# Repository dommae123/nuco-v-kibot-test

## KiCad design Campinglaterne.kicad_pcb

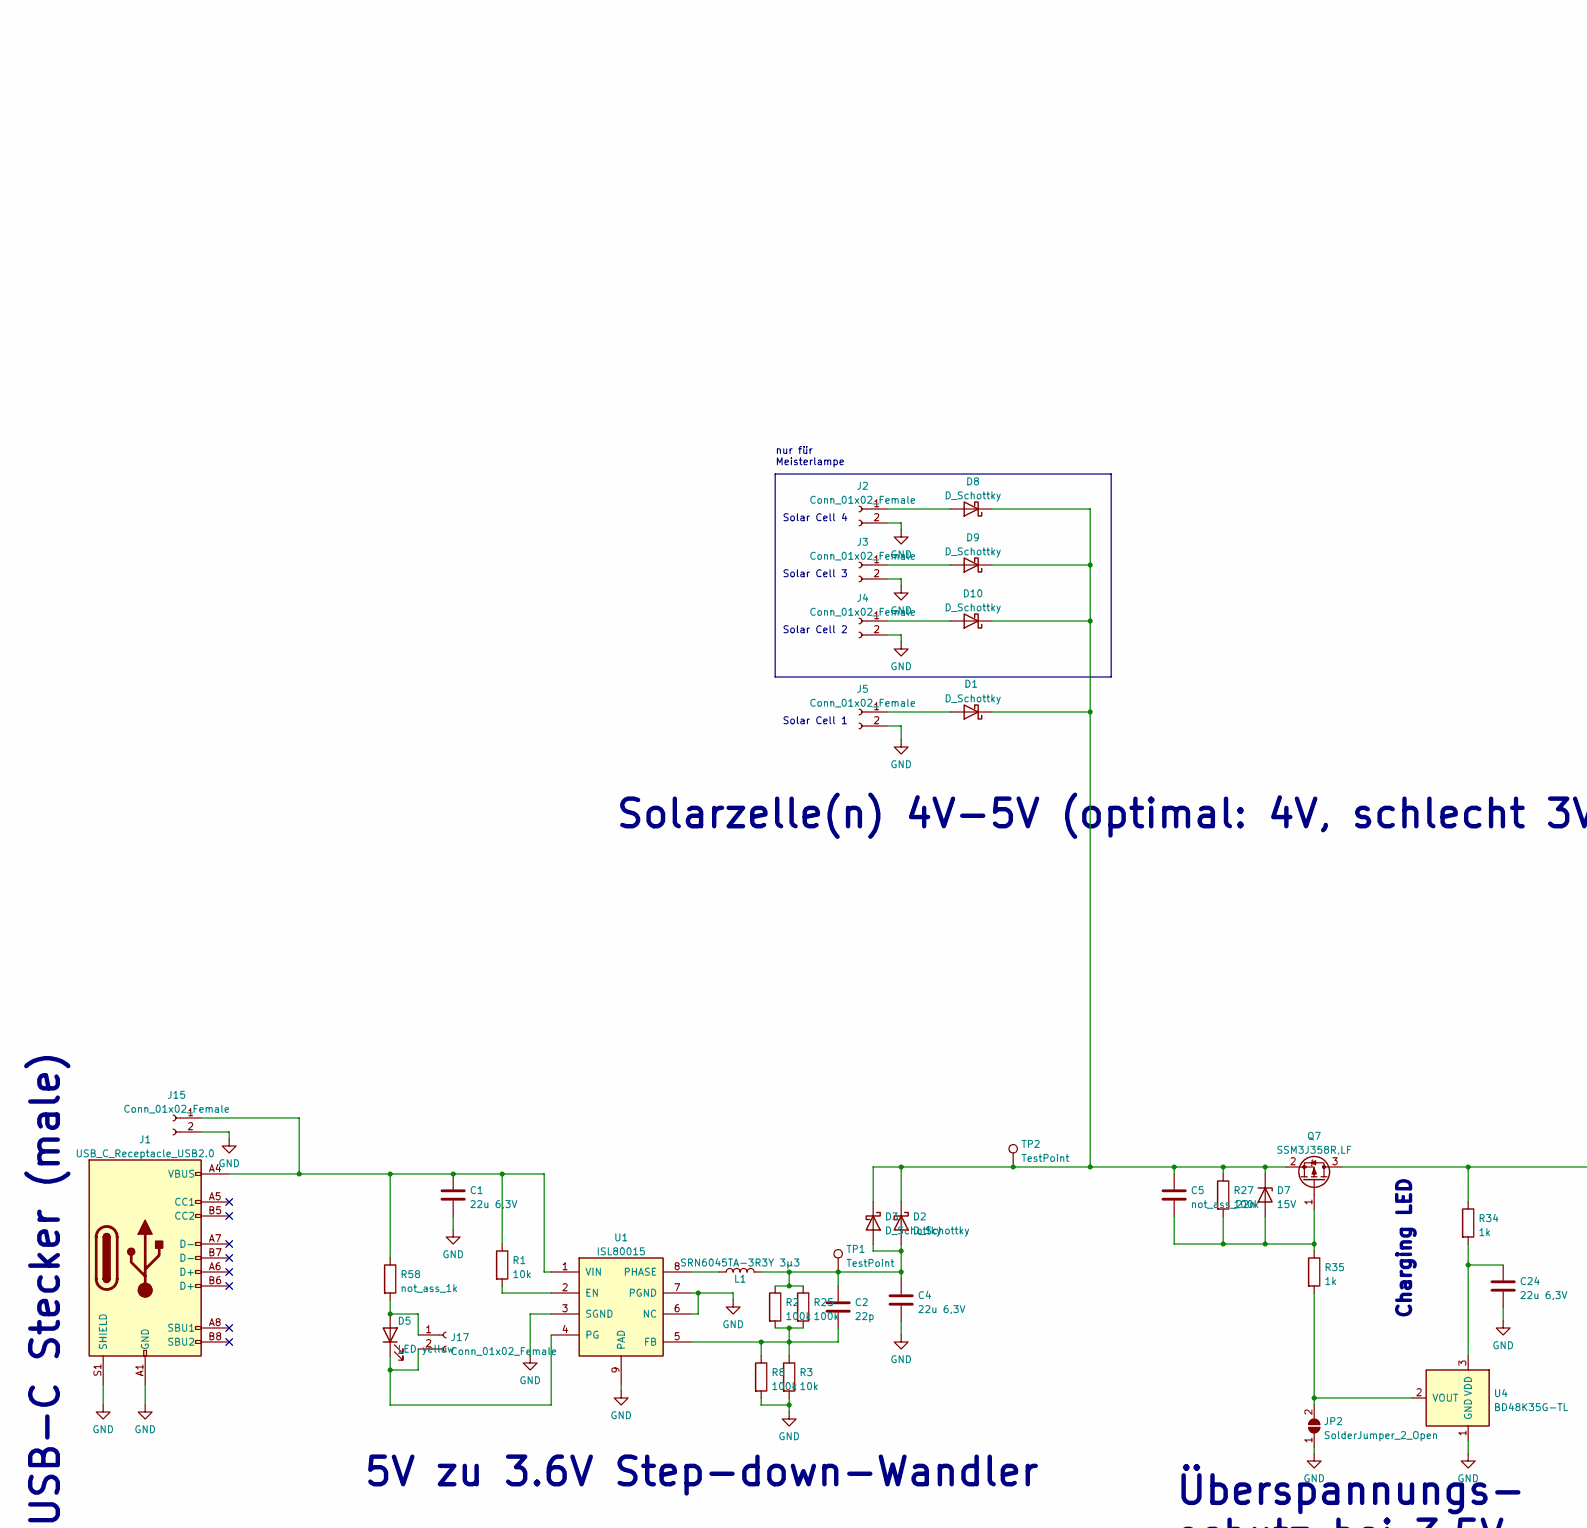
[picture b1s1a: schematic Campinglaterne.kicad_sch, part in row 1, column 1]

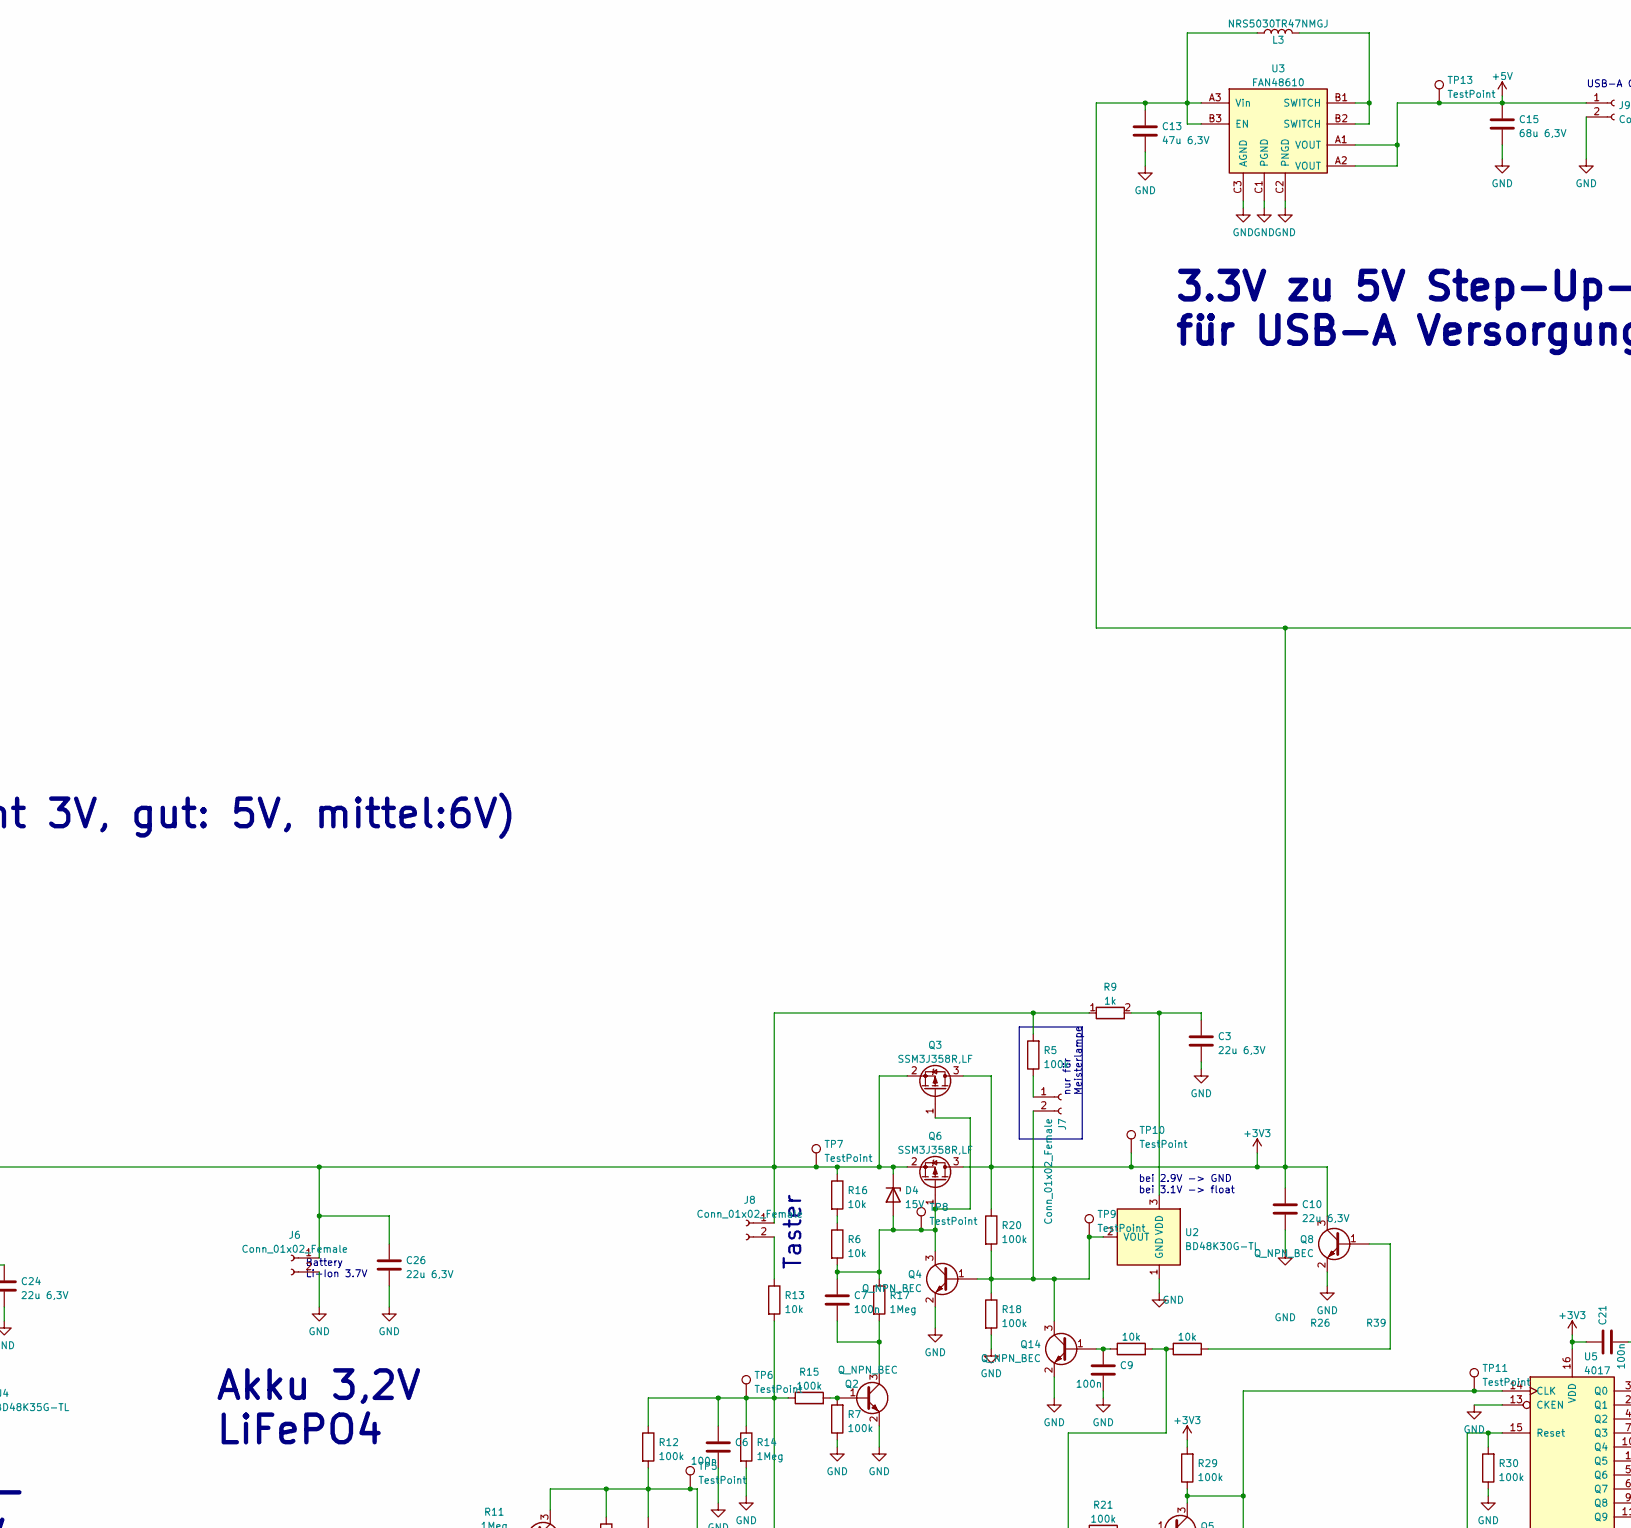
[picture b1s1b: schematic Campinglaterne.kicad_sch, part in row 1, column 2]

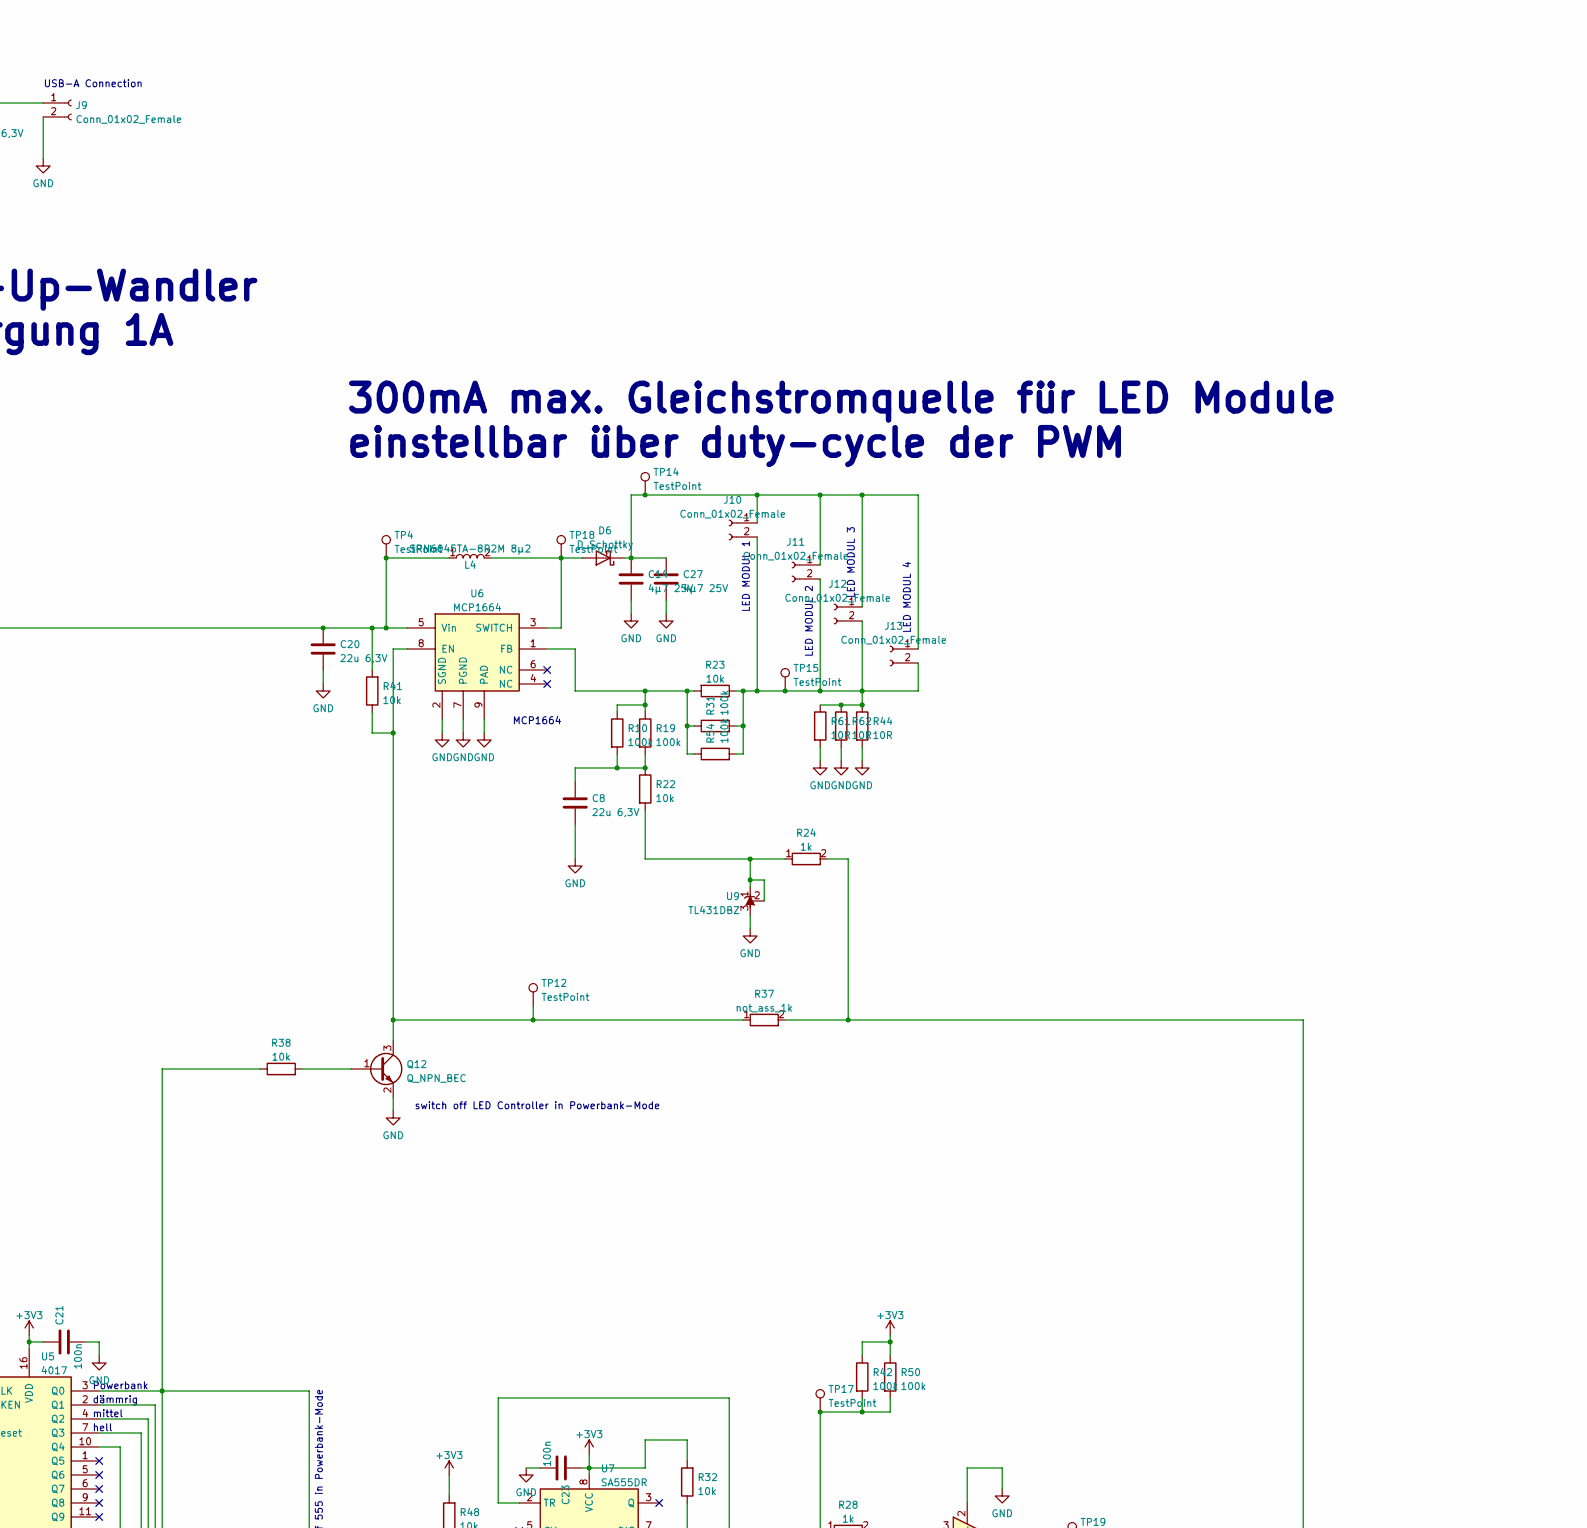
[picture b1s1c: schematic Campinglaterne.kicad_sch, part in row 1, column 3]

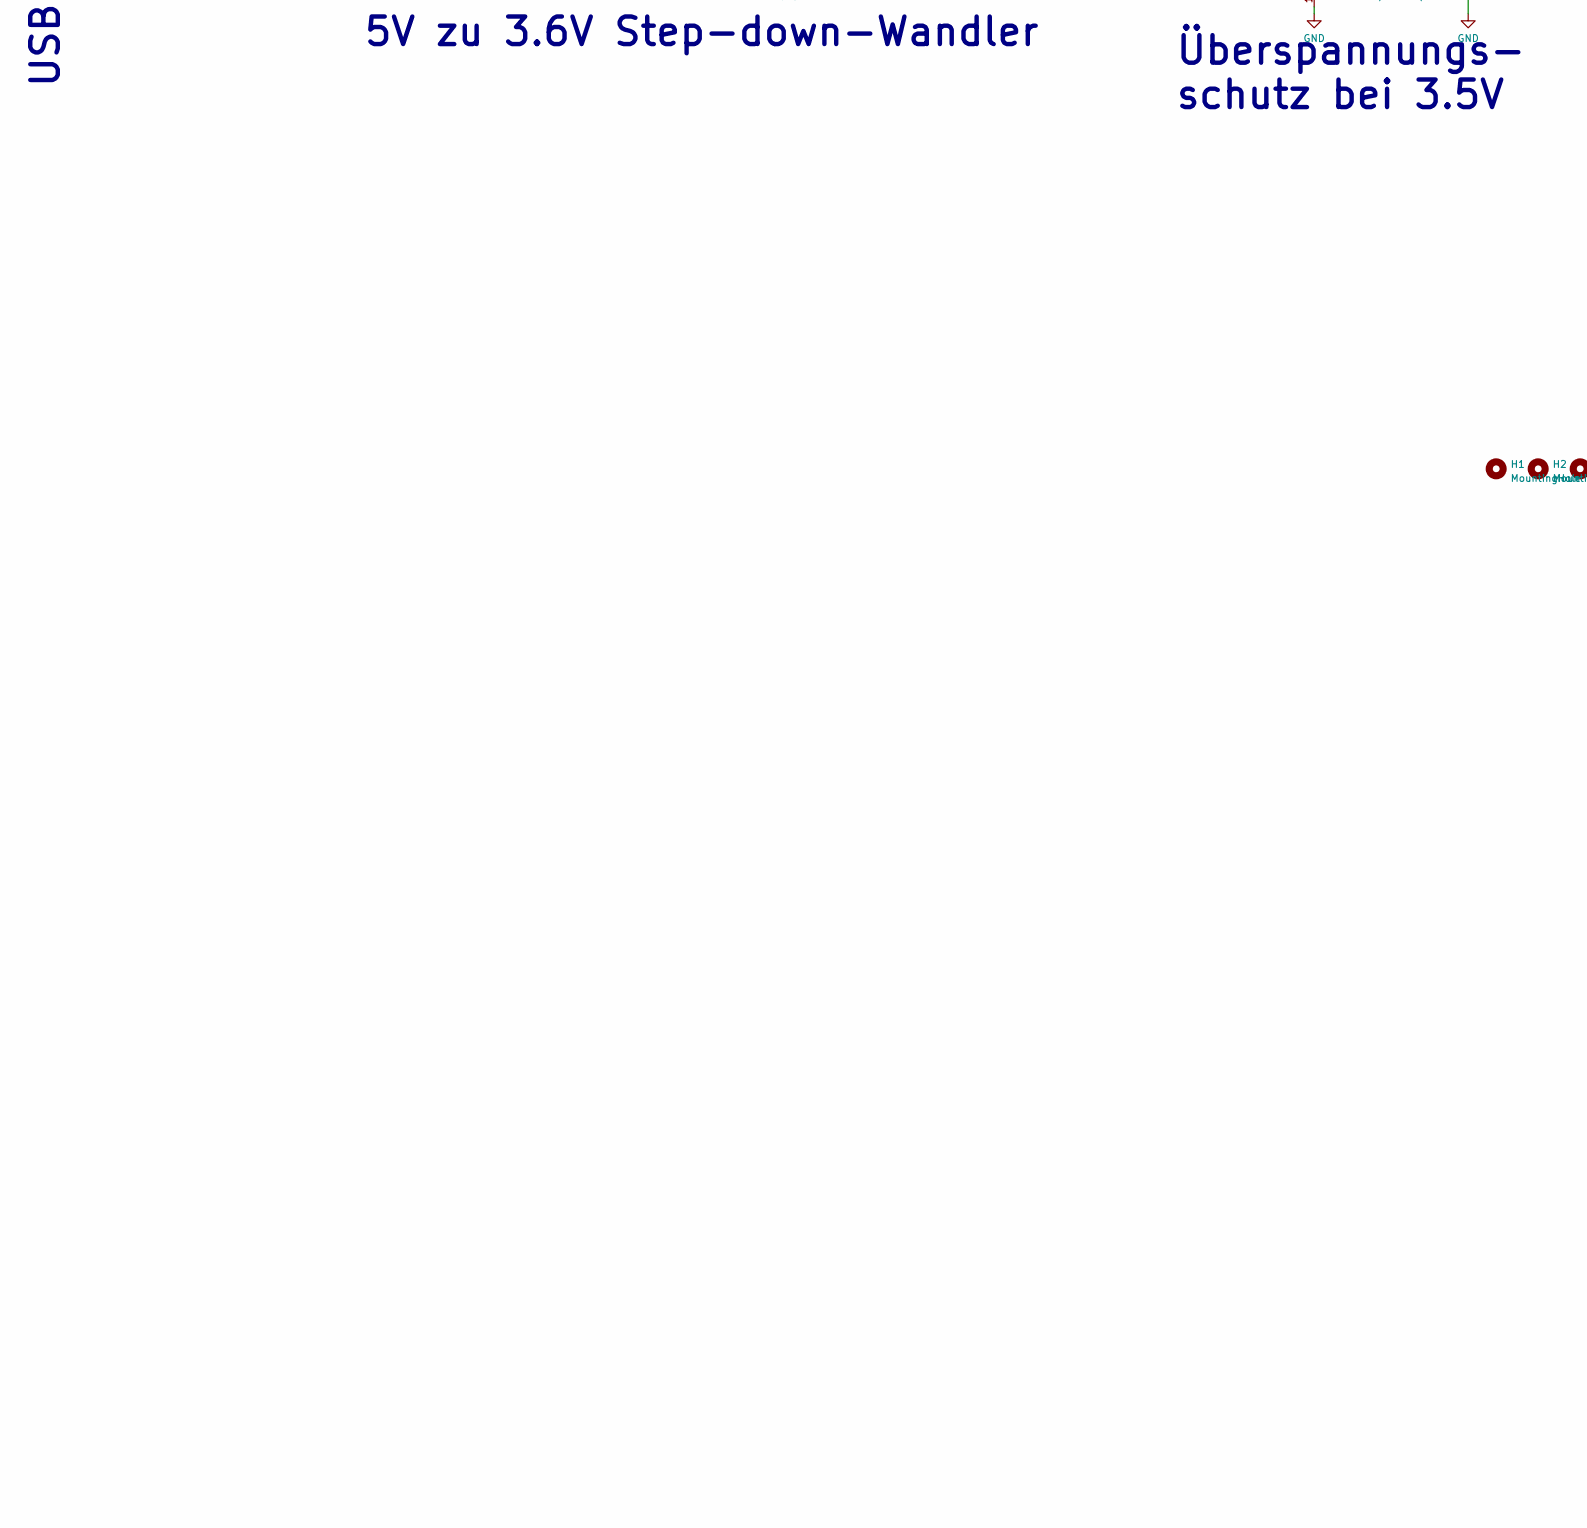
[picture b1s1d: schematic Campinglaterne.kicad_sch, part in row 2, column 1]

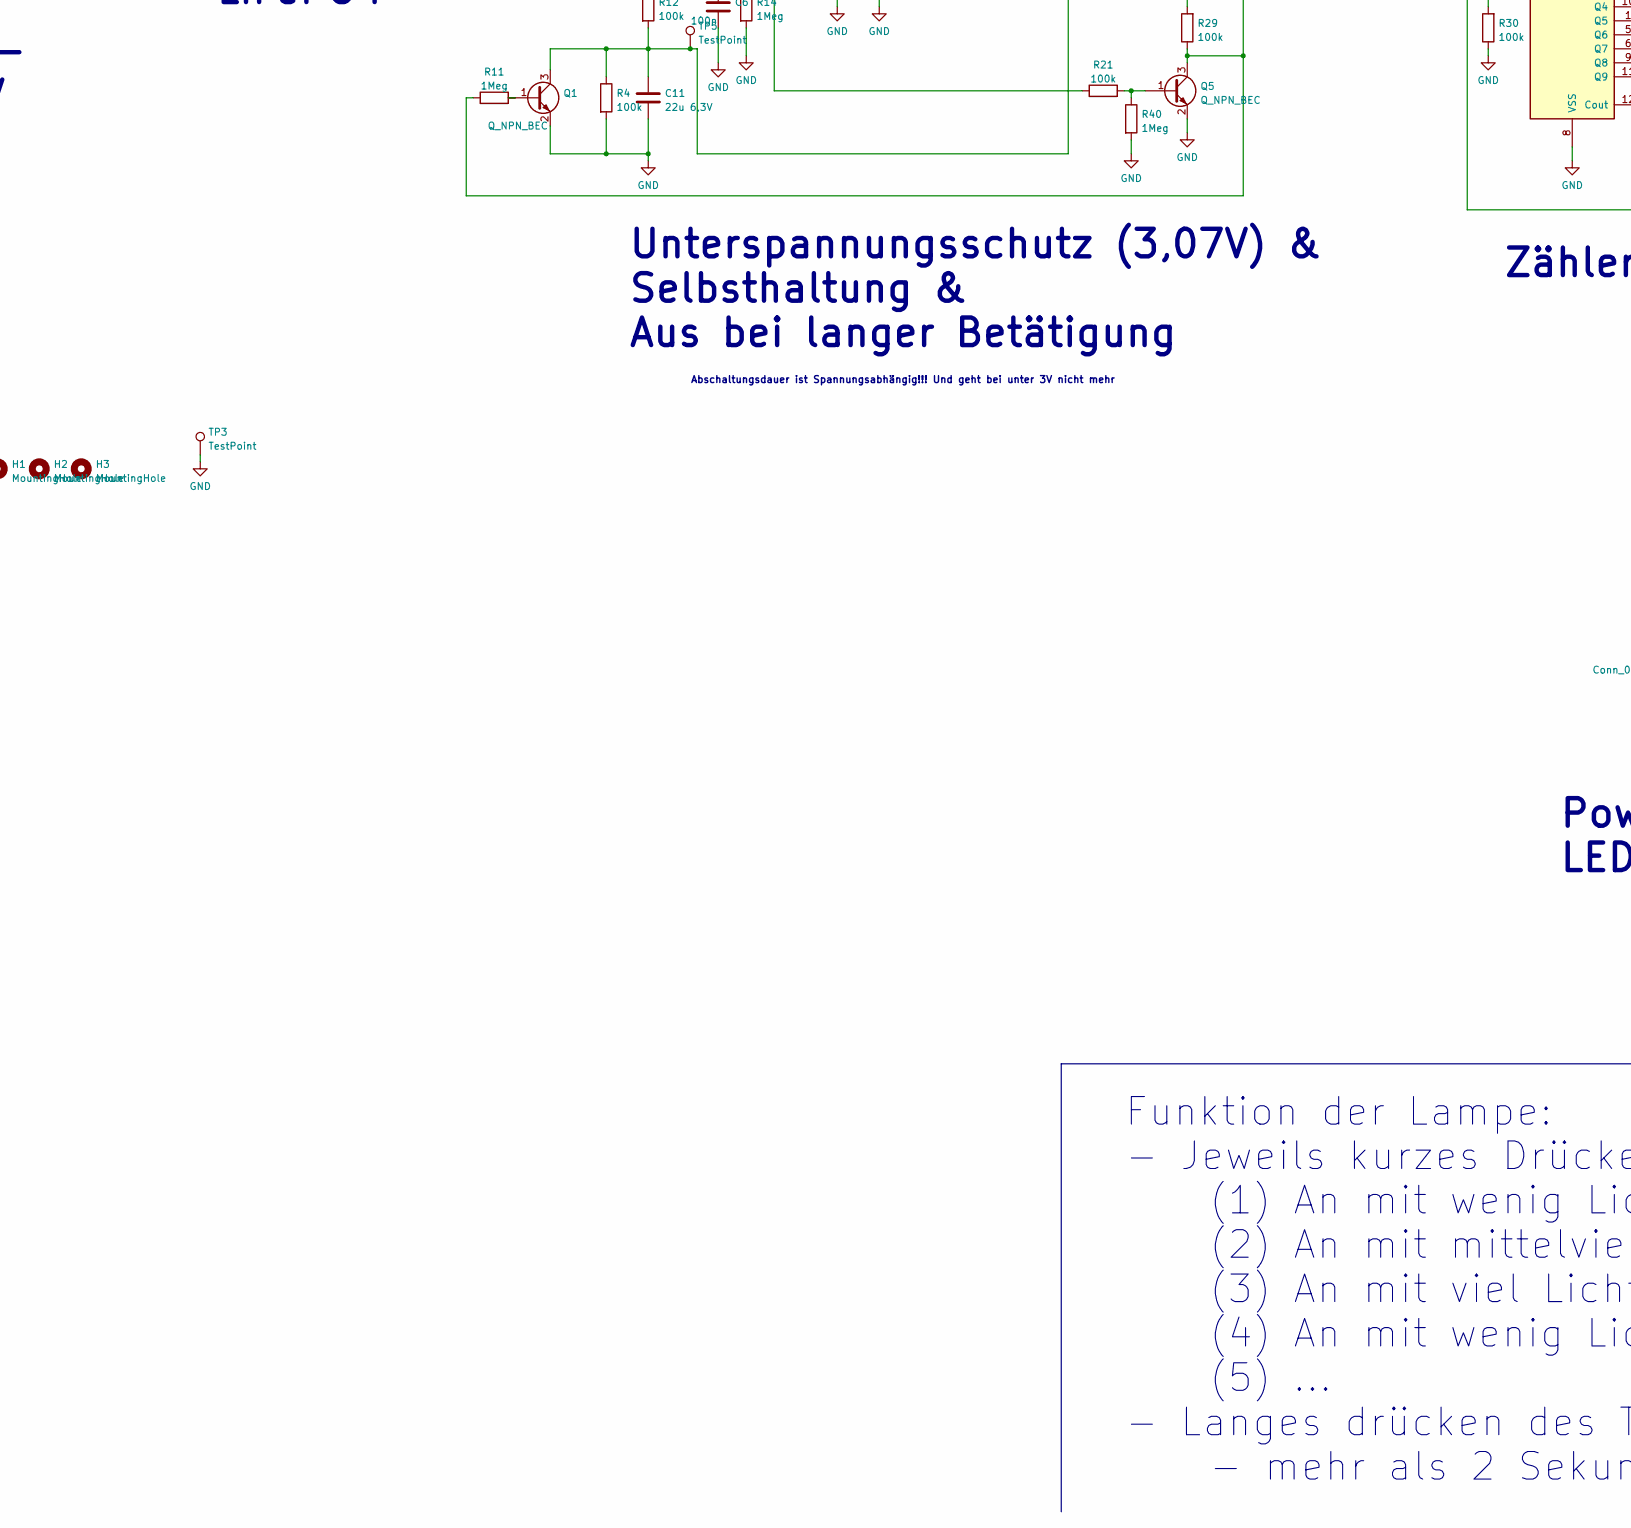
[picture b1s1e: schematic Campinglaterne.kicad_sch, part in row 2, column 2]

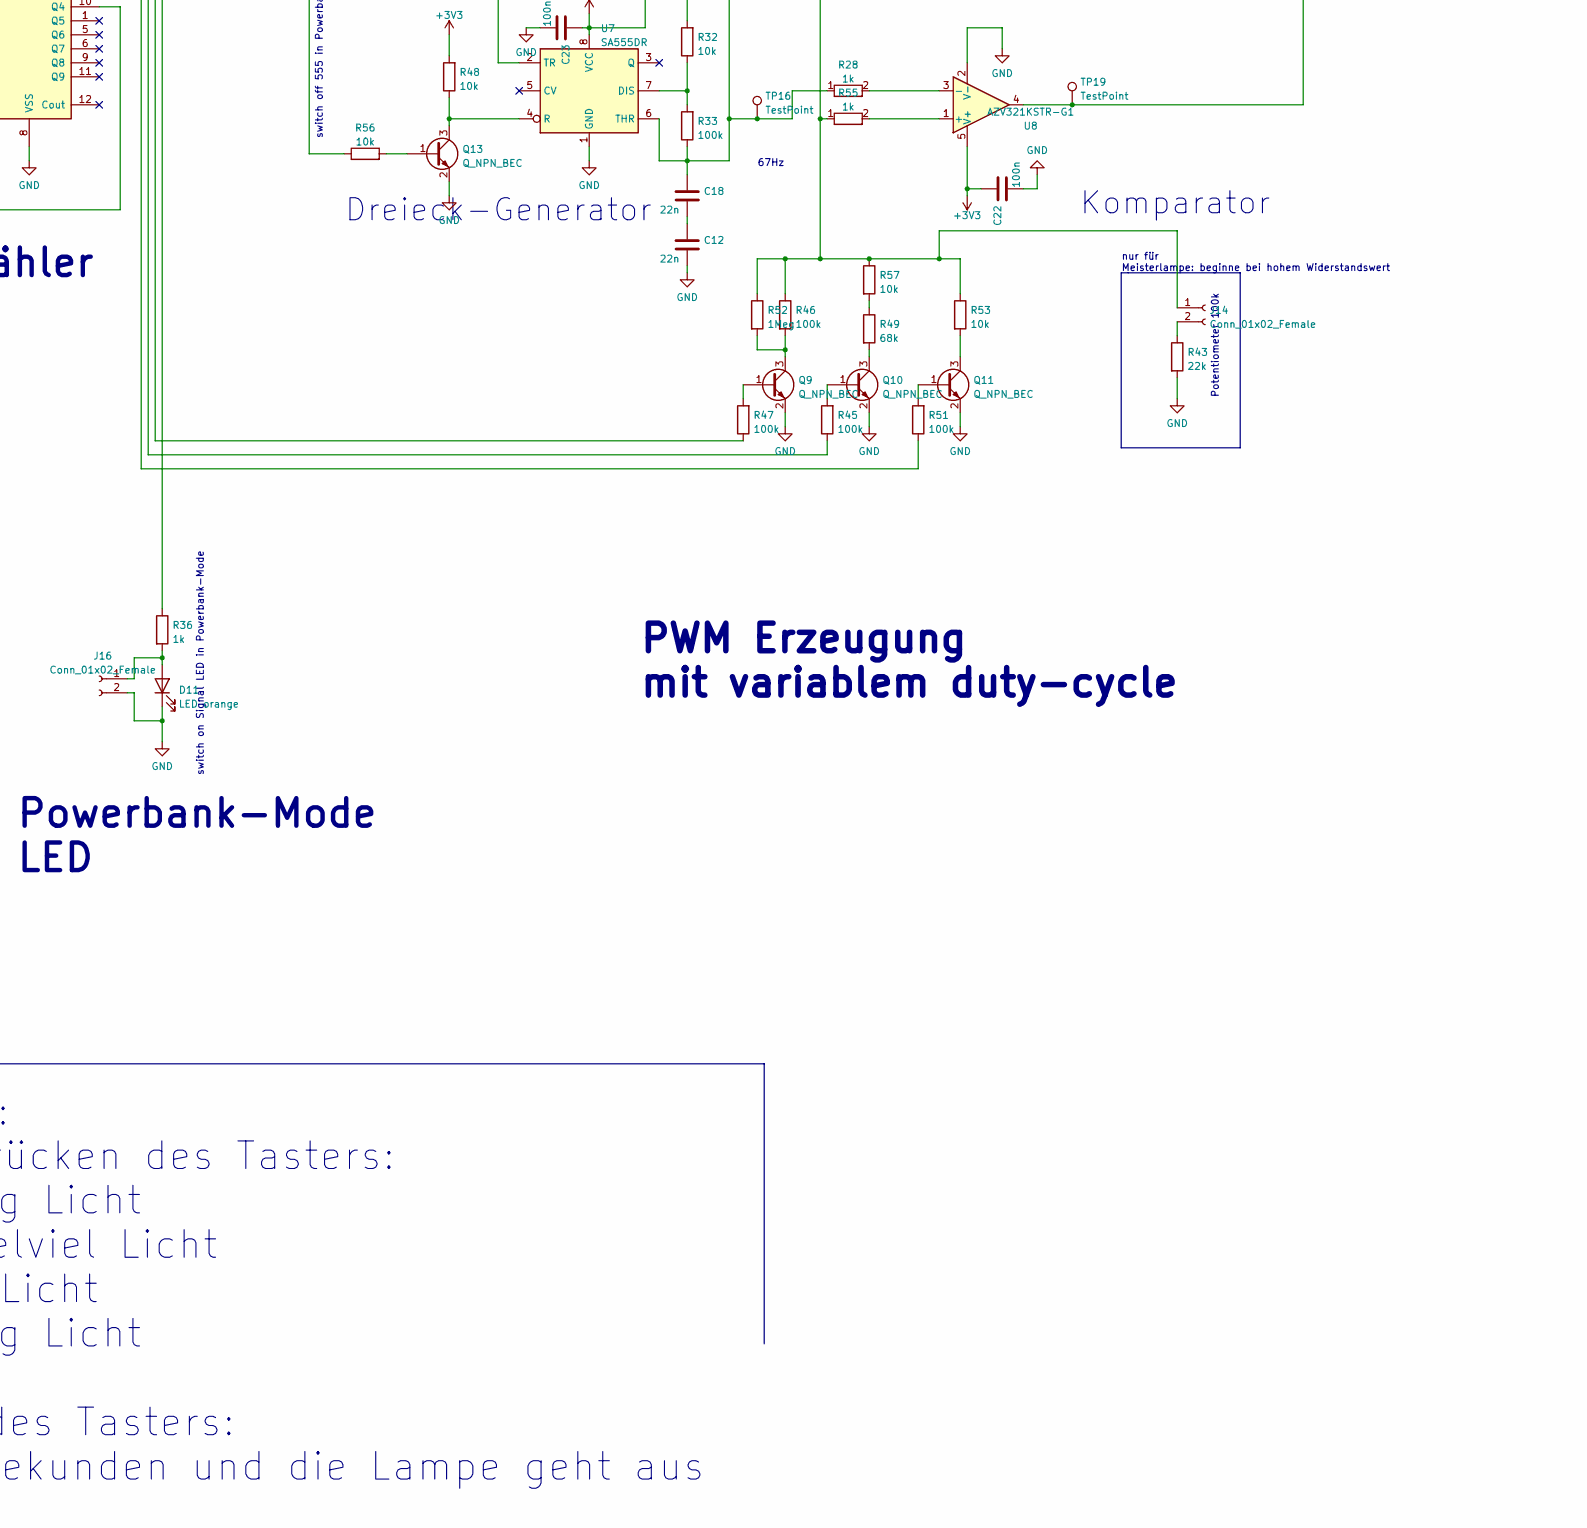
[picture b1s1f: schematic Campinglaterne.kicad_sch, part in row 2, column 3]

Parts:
C1, C3, C4, C8, C10, C11, C20, C24, C26: 22u 6,3V; C_0603_1608Metric
C2: 22p; C_0603_1608Metric
C5: not_ass_22n; C_0603_1608Metric
C6, C7, C9, C21, C22, C23: 100n; C_0603_1608Metric
C12, C18: 22n; C_0603_1608Metric
C13: 47u 6,3V; C_0603_1608Metric
C14, C27: 4µ7 25V; C_0805_2012Metric
C15: 68u 6,3V; C_0603_1608Metric
D1, D8, D9, D10: D_Schottky; D_0805_2012Metric
D2, D3, D6: D_Schottky; D_SMB
D4, D7: 15V; D_SOT-23_ANK
D5: LED yellow; LED_0603_1608Metric
D11: LED orange; LED_0603_1608Metric
H1, H2, H3: MountingHole; MountingHole_3.2mm_M3_ISO14580
J1: USB_C_Receptacle_USB2.0; USB_C_Receptacle_GCT_USB4085
J2, J3, J4, J5, J6, J7, J8, J9, J10, J11, J12, J13, J14, J15, J16, J17: Conn_01x02_Female; PinSocket_1x02_P2.54mm_Vertical
JP2: SolderJumper_2_Open; SolderJumper-2_P1.3mm_Open_RoundedPad1.0x1.5mm
L1: SRN6045TA-3R3Y 3µ3; L_Bourns_SRN6045TA
L3: NRS5030TR47NMGJ; L_Taiyo-Yuden_NR-50xx
L4: SRN6045TA-8R2M 8µ2; L_Bourns_SRN6045TA
Q1, Q2, Q4, Q5, Q8, Q9, Q10, Q11, Q12, Q13, Q14: Q_NPN_BEC; SOT-23
Q3, Q6, Q7: SSM3J358R,LF; SOT-23
R1, R3, R6, R13, R16, R22, R23, R26, R32, R38, R39, R41, R48, R53, R56, R57: 10k; R_0603_1608Metric
R2, R4, R5, R7, R8, R10, R12, R15, R18, R19, R20, R21, R25, R27, R29, R30, R31, R33, R42, R45, R46, R47, R50, R51, R54: 100k; R_0603_1608Metric
R9, R24, R28, R34, R35, R36, R55: 1k; R_0603_1608Metric
R11, R14, R17, R40, R52: 1Meg; R_0603_1608Metric
R37, R58: not_ass_1k; R_0603_1608Metric
R43: 22k; R_0603_1608Metric
R44, R61, R62: 10R; R_0603_1608Metric
R49: 68k; R_0603_1608Metric
TP1, TP2, TP3, TP4, TP5, TP6, TP7, TP8, TP9, TP10, TP11, TP12, TP13, TP14, TP15, TP16, TP17, TP18, TP19: TestPoint; TestPoint_THTPad_2.0x2.0mm_Drill1.0mm
U1: ISL80015; DFN-8-1EP_2x2mm_P0.5mm_EP0.8x1.6mm
U2: BD48K30G-TL; SOT-23
U3: FAN48610; Maxim_WLP-9_1.595x1.415_Layout3x3_P0.4mm_Ball0.27mm_Pad0.25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
U4: BD48K35G-TL; SOT-23
U5: 4017; SOIC-16_4.55x10.3mm_P1.27mm
U6: MCP1664; DFN-8-1EP_3x2mm_P0.5mm_EP1.3x1.5mm
U7: SA555DR; SOIC-8_3.9x4.9mm_P1.27mm
U8: AZV321KSTR-G1; SOT-23-5
U9: TL431DBZ; SOT-23

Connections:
+3V3: C10.1, C13.1, C20.1, C21.1, C22.1, C23.1, L3.1, L4.1, Q3.3 (D), Q6.3 (D), Q8.3 (C), R20.1, R29.2, R32.2, R41.2, R42.1, R48.2, R50.1, TP4.1, TP10.1, U3.A3 (Vin), U3.B3 (EN), U5.16 (VDD), U6.5 (Vin), U7.8 (VCC), U8.5 (V+)
+5V: C15.1, J9.1, TP13.1, U3.A1 (VOUT), U3.A2 (VOUT)
GND: C1.2, C3.2, C4.2, C6.2, C8.2, C9.2, C10.2, C11.2, C12.2, C13.2, C14.2, C15.2, C20.2, C21.2, C22.2, C23.2, C24.2, C26.2, C27.2, D11.1 (K), J1.A1 (GND), J1.A12 (GND), J1.B1 (GND), J1.B12 (GND), J1.S1 (SHIELD), J2.2, J3.2, J4.2, J5.2, J6.2, J9.2, J15.2, J16.2, JP2.1 (A), Q1.2 (E), Q2.2 (E), Q4.2 (E), Q5.2 (E), Q8.2 (E), Q9.2 (E), Q10.2 (E), Q11.2 (E), Q12.2 (E), Q13.2 (E), Q14.2 (E), R3.2, R4.2, R7.1, R8.2, R14.2, R18.2, R30.1, R40.2, R43.2, R44.2, R61.2, R62.2, TP3.1, U1.3 (SGND), U1.6 (NC), U1.7 (PGND), U1.9 (PAD), U2.1 (GND), U3.C1 (PGND), U3.C2 (PNGD), U3.C3 (AGND), U4.1 (GND), U5.8 (VSS), U5.13 (CKEN), U6.2 (SGND), U6.7 (PGND), U6.9 (PAD), U7.1 (GND), U8.2 (V-), U9.3 (A)
unnamed: C1.1, J1.A4 (VBUS), J1.A9 (VBUS), J1.B4 (VBUS), J1.B9 (VBUS), J15.1, R1.1, R58.1, U1.1 (VIN)
unnamed: C2.1, C4.1, D2.2 (A), D3.2 (A), L1.2, R2.1, R25.1, TP1.1
unnamed: C2.2, R2.2, R3.1, R8.1, R25.2, U1.5 (FB)
unnamed: C3.1, R9.2, U2.3 (VDD)
unnamed: C5.1, D1.1 (K), D2.1 (K), D3.1 (K), D7.1 (K), D8.1 (K), D9.1 (K), D10.1 (K), Q7.2 (S), R27.1, TP2.1
unnamed: C5.2, D7.2 (A), Q7.1 (G), R27.2, R35.1
unnamed: C6.1, R12.1, R13.2, R14.1, R15.1, R21.1, TP6.1
unnamed: C7.1, D4.2 (A), Q3.1 (G), Q4.3 (C), Q6.1 (G), R6.2, R17.1, TP8.1
unnamed: C7.2, Q2.3 (C), R17.2
unnamed: C8.1, R10.2, R19.2, R22.1
unnamed: C9.1, Q14.1 (B), R26.1
unnamed: C11.1, Q1.3 (C), R4.1, R12.2, R26.2, R39.1, TP5.1
unnamed: C12.1, C18.2
unnamed: C14.1, C27.1, D6.1 (K), J10.1, J11.1, J12.1, J13.1, TP14.1
unnamed: C18.1, R28.1, R33.1, TP16.1, U7.2 (TR), U7.6 (THR)
unnamed: C24.1, R34.2, U4.3 (VDD)
unnamed 19: C26.1, D4.1 (K), J6.1, J8.1, Q3.2 (S), Q6.2 (S), Q7.3 (D), R5.2, R9.1, R16.1, R34.1, TP7.1; also elsewhere on the board
unnamed: D1.2 (A), J5.1
unnamed: D6.2 (A), L4.2, TP18.1, U6.3 (SWITCH)
unnamed: D8.2 (A), J2.1
unnamed: D9.2 (A), J3.1
unnamed: D10.2 (A), J4.1
unnamed: D11.2 (A), J16.1, R36.2
unnamed 26: D5.2 (A), J17.1, R58.2; also elsewhere on the board
unnamed: J7.1, R5.1
unnamed: J7.2, Q4.1 (B), Q14.3 (C), R18.1, R20.2, TP9.1, U2.2 (VOUT)
unnamed: J8.2, R13.1
unnamed: J10.2, J11.2, J12.2, J13.2, R23.1, R31.2, R44.1, R54.2, R61.1, R62.1, TP15.1
unnamed: J14.1, R42.2, R46.1, R50.2, R52.1, R53.1, R55.1, R57.1, TP17.1
unnamed: J14.2, R43.1
unnamed: L1.1, U1.8 (PHASE)
unnamed: L3.2, U3.B1 (SWITCH), U3.B2 (SWITCH)
unnamed: Q1.1 (B), R11.2
unnamed: Q2.1 (B), R7.2, R15.2
unnamed: Q5.1 (B), R21.2, R40.1
unnamed: Q5.3 (C), R11.1, R29.1, TP11.1, U5.14 (CLK)
unnamed: Q8.1 (B), R39.2
unnamed: Q9.1 (B), R47.2
unnamed: Q9.3 (C), R46.2, R52.2
unnamed: Q10.1 (B), R45.2
unnamed: Q10.3 (C), R49.2
unnamed: Q11.1 (B), R51.2
unnamed: Q11.3 (C), R53.2
unnamed: Q12.1 (B), R38.2
unnamed: Q12.3 (C), R37.1, R41.1, TP12.1, U6.8 (EN)
unnamed: Q13.1 (B), R56.2
unnamed: Q13.3 (C), R48.1, U7.4 (R)
unnamed: R1.2, U1.2 (EN)
unnamed: R10.1, R19.1, R23.2, R31.1, R54.1, U6.1 (FB)
unnamed: R6.1, R16.2
unnamed: R22.2, R24.1, U9.1 (K), U9.2 (REF)
unnamed: R24.2, R37.2, TP19.1, U8.4
unnamed: R28.2, U8.3 (-)
unnamed: R30.2, U5.10 (Q4), U5.15 (Reset)
unnamed: R32.1, R33.2, U7.7 (DIS)
unnamed: R36.1, R38.1, R56.1, U5.3 (Q0)
unnamed: R45.1, U5.4 (Q2)
unnamed: R47.1, U5.2 (Q1)
unnamed: R49.1, R57.2
unnamed: R51.1, U5.7 (Q3)
unnamed: R55.2, U8.1 (+)

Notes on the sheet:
Funktion der Lampe: - Jeweils kurzes Drücken des Tasters: (1) An mit wenig Licht (2) An mit mittelviel Licht (3) An mit viel Licht (4) An mit wenig Licht (5) ... - Langes drücken des Tasters: - mehr als 2 Sekunden und die Lampe geht aus
dämmrig
Solar Cell 3
Komparator
MCP1664
hell
nur für Meisterlampe: beginne bei hohem Widerstandswert
Powerbank-Mode LED
switch off 555 in Powerbank-Mode
mittel
300mA max. Gleichstromquelle für LED Module einstellbar über duty-cycle der PWM
LED MODUL 4
Potentiometer 100k
switch off LED Controller in Powerbank-Mode
Zähler
Powerbank
bei 2.9V -> GND bei 3.1V -> float
Battery Li-Ion 3.7V
Solar Cell 2
USB-C Stecker (male)
Solar Cell 1
Akku 3,2V LiFePO4
3.3V zu 5V Step-Up-Wandler für USB-A Versorgung 1A
67Hz
Solar Cell 4
Überspannungs- schutz bei 3.5V
5V zu 3.6V Step-down-Wandler
Taster
Unterspannungsschutz (3,07V) & Selbsthaltung & Aus bei langer Betätigung
USB-A Connection
LED MODUL 2
Abschaltungsdauer ist Spannungsabhängig!!! Und geht bei unter 3V nicht mehr
switch on Signal LED in Powerbank-Mode
LED MODUL 3
LED MODUL 1
PWM Erzeugung mit variablem duty-cycle
Dreieck-Generator
Solarzelle(n) 4V-5V (optimal: 4V, schlecht 3V, gut: 5V, mittel:6V)
nur für Meisterlampe
Charging LED

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
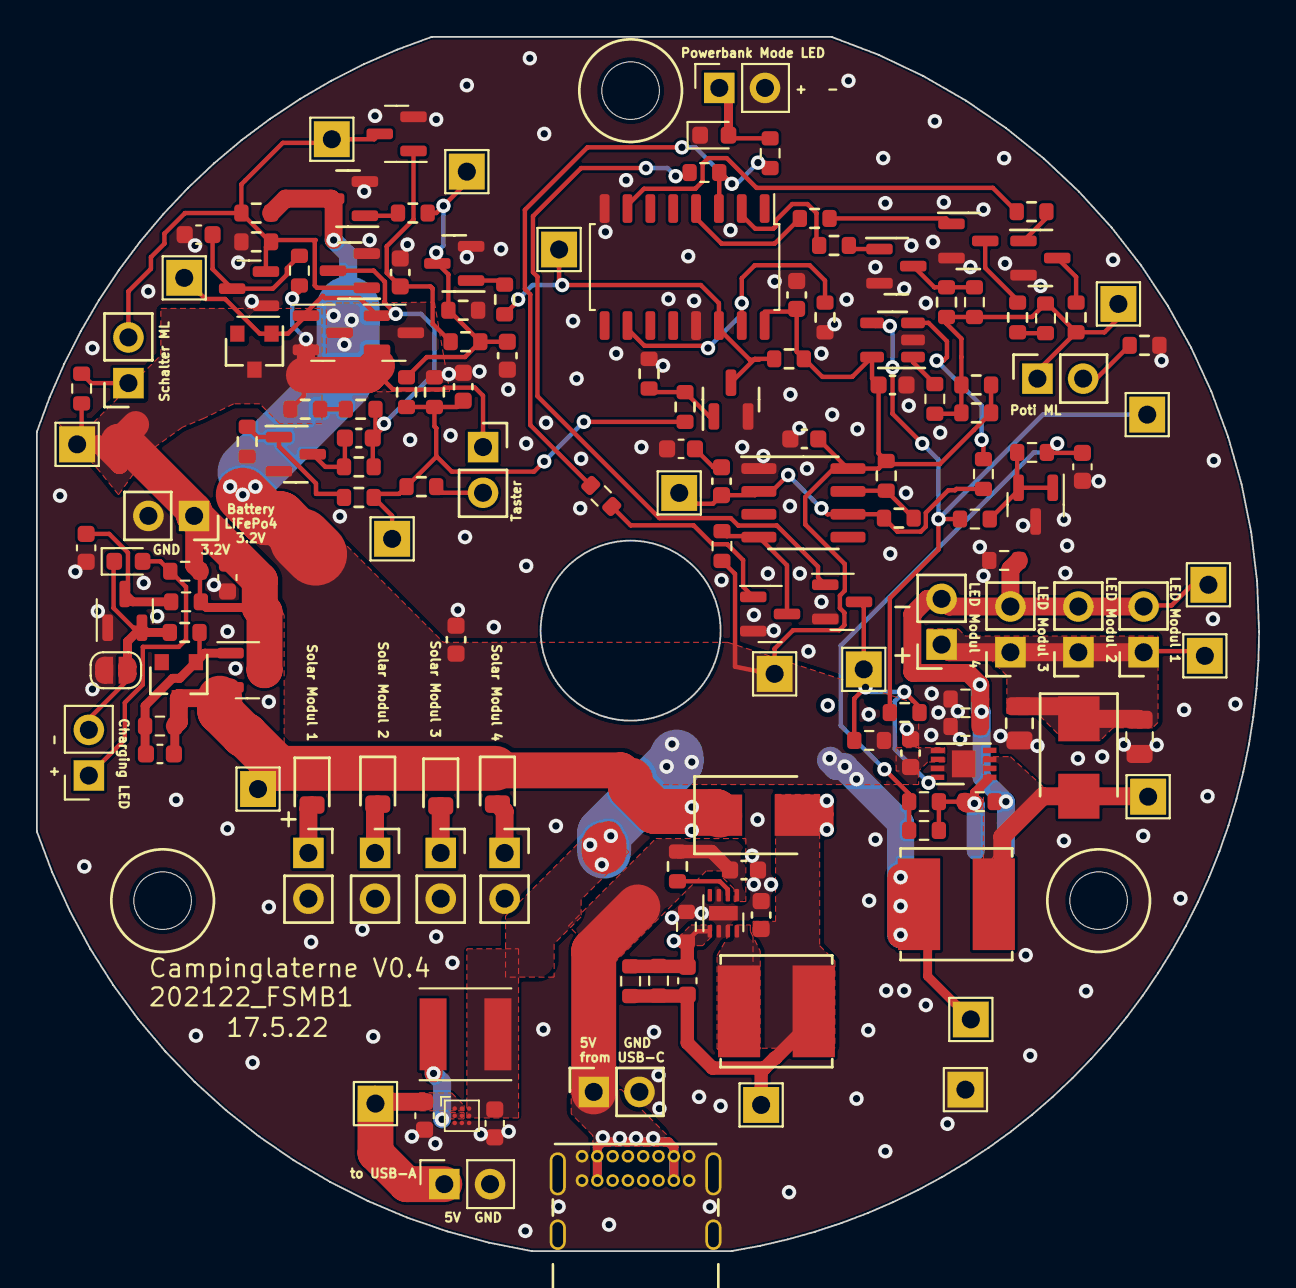
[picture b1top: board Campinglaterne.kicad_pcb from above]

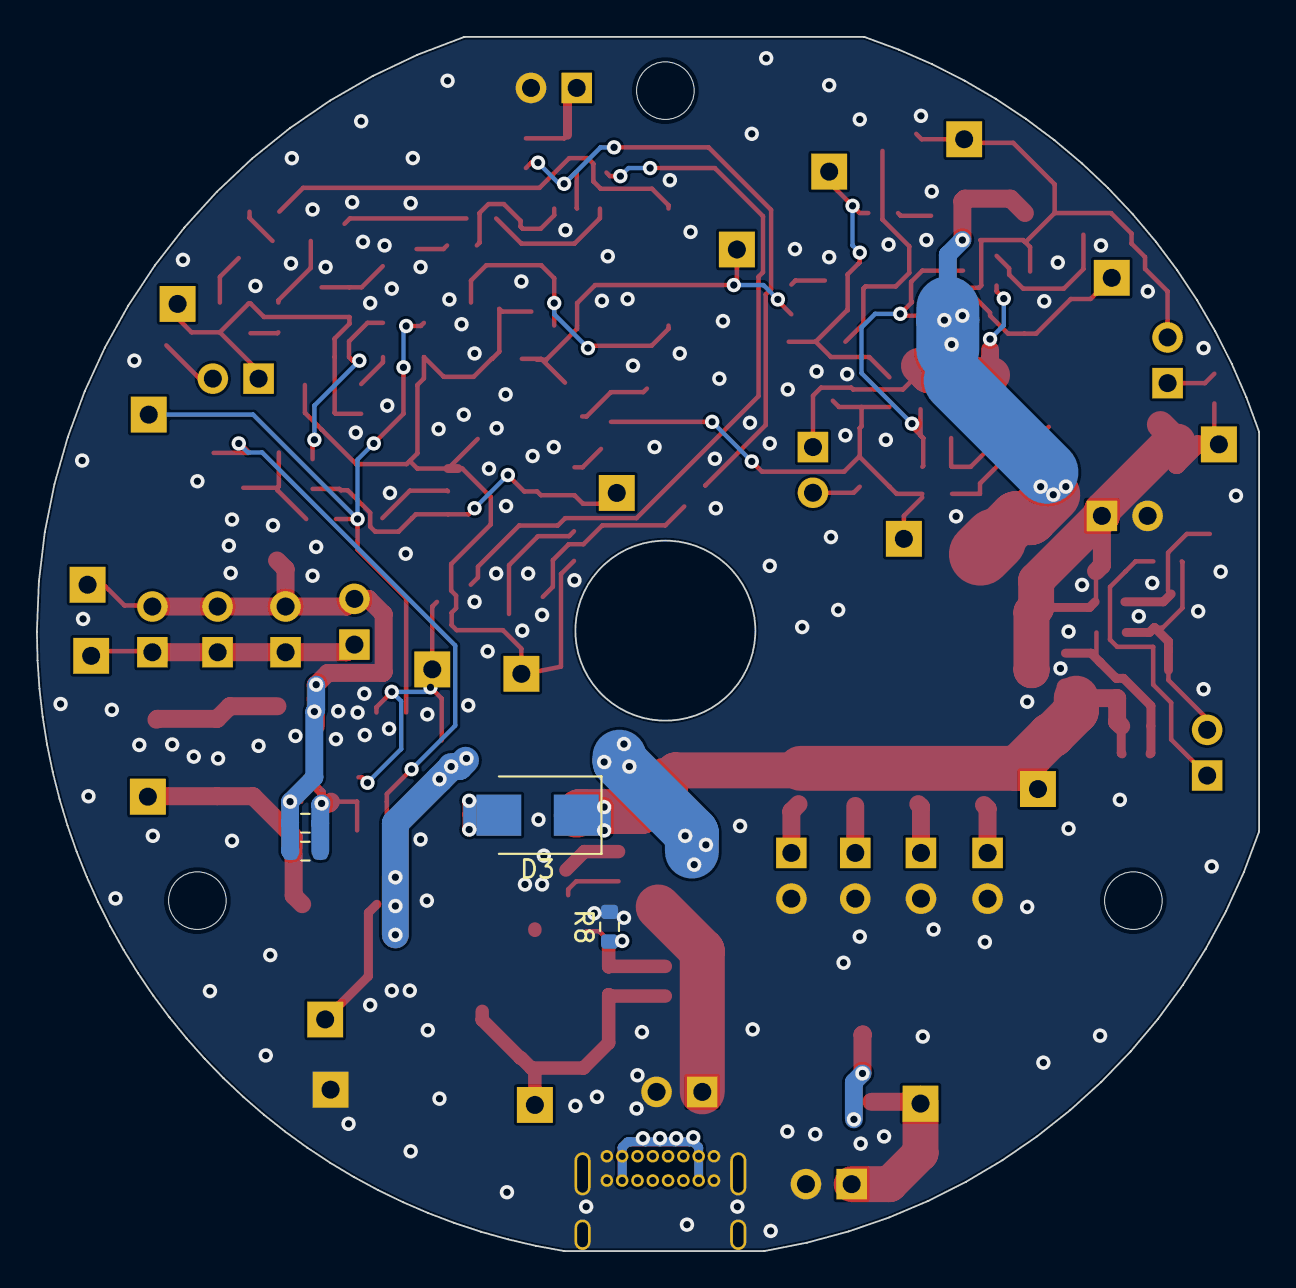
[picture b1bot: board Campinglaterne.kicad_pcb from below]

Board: 2 copper layers, 67.9 x 67.5 mm, 160 parts (4 on the bottom side), 65 nets.

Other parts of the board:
D12: LED yellow; LED_0603_1608Metric
R63: not_ass_1k; R_0603_1608Metric

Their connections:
unnamed 19: R63.1; also elsewhere on the board
unnamed 26: D12.2 (A), R63.2; also elsewhere on the board

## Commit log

2022-06-21 Set up CI with Azure Pipelines
    [skip ci]
